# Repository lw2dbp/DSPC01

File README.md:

# DSPC01-Adapter
Pcb adapter dspc01

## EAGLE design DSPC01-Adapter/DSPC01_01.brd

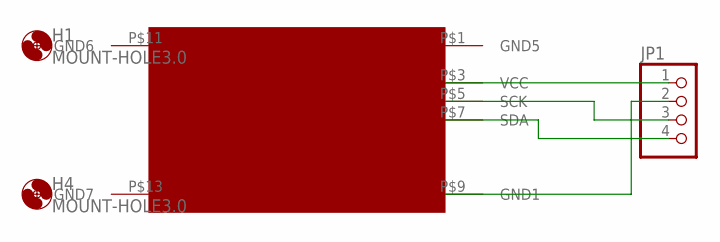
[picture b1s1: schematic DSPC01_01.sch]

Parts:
H1, H4: MOUNT-HOLE3.0; 3,0
JP1: PINHD-1X4/90; 1X04/90
U$1: DSPC01

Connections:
unnamed: JP1.2, U$1.P$9 (GND1)
unnamed: JP1.1, U$1.P$3 (VCC)
unnamed: JP1.3, U$1.P$5 (SCK)
unnamed: JP1.4, U$1.P$7 (SDA)

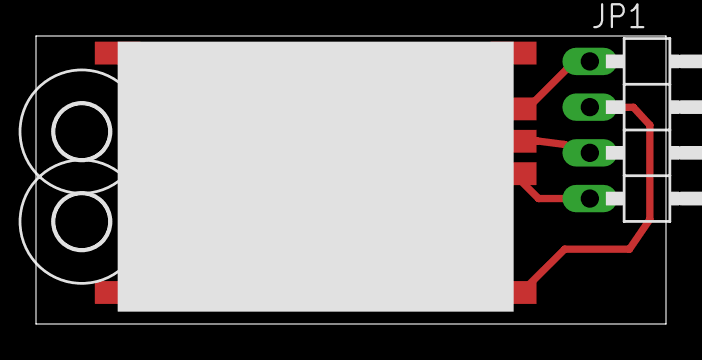
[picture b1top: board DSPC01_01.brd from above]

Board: 2 copper layers, 35.0 x 16.0 mm, 4 parts (0 on the bottom side), 4 nets.

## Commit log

2015-08-21 Version original
